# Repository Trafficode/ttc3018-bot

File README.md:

# Bark Beetle

Rebuildable configuration for a Raspberry Pi CNC monitoring host.
Current baseline: Raspberry Pi 5, Raspberry Pi Camera Rev 1.3 (OV5647),
DHT22 on GPIO17 and private Tailscale access.

- [Set up another Raspberry Pi](docs/development/setup.md)
- [Run checks and troubleshoot](docs/development/operations.md)
- [Verified hardware and software](docs/reference/baseline.md)
- [System boundaries and next components](docs/architecture/system.md)
- [Build and operate the component-based panel](docs/development/operator-ui.md)
- [Local manufacturing collection and Tractor transfer](docs/development/file-library.md)
- [Install the private Android operator app](docs/development/android-app.md)
- [Plan PCB surface measurements](docs/development/surface-plan.md)
- [Check the probe and set automatic Z zero](docs/development/z-probe.md)
- [10 mm PCB starter coupon and CAM files](docs/reference/pcb-cnc-coupon-10mm-cam.md)
- [40 mm PCB reference coupon](docs/reference/pcb-cnc-coupon-40mm.md)

Bark Beetle provides camera video, environmental telemetry and explicit manual CNC
controls through private Tailscale Serve. The operator connects USB, jogs, sets
material zero and controls the spindle. There is no automatic USB reconnect,
homing or unlock. Z probing starts only with operator confirmation and a verified
probe-input test. File jobs support explicitly started linear GRBL
programs; see [file jobs and limits](docs/development/file-jobs.md).
See the operations guide for the first supervised test.

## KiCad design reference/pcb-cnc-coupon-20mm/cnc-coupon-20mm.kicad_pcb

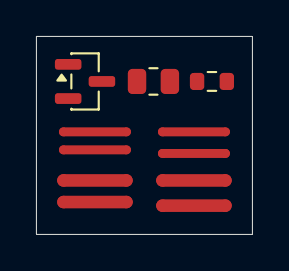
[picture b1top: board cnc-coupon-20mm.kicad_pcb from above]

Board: 2 copper layers, 12.0 x 11.0 mm, 7 parts (0 on the bottom side), 8 nets.

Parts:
Q1: SOT-23
R1: R_0805_2012Metric
R2: R_0603_1608Metric
T1: W0.5_G0.5; Pair_W0.5_G0.5
T2: W0.5_G0.7; Pair_W0.5_G0.7
T3: W0.7_G0.5; Pair_W0.7_G0.5
T4: W0.7_G0.7; Pair_W0.7_G0.7

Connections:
W0.5_G0.5_1: T1.1, T1.2
W0.5_G0.5_2: T1.3, T1.4
W0.5_G0.7_1: T2.1, T2.2
W0.5_G0.7_2: T2.3, T2.4
W0.7_G0.5_1: T3.1, T3.2
W0.7_G0.5_2: T3.3, T3.4
W0.7_G0.7_1: T4.1, T4.2
W0.7_G0.7_2: T4.3, T4.4

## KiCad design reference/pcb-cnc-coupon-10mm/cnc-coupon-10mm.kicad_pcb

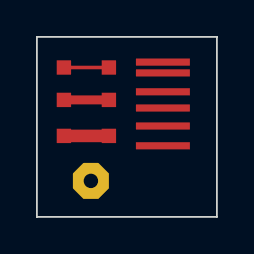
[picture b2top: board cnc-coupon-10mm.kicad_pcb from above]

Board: 2 copper layers, 10.0 x 10.0 mm, 7 parts (0 on the bottom side), 3 nets.

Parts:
G1: Gap_0.2mm
G2: Gap_0.5mm
G3: Gap_0.7mm
V1: Octagon_2mm_Drill_0.8mm
W1: Width_0.2mm
W2: Width_0.5mm
W3: Width_0.7mm

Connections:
WIDTH_0.2: W1.1, W1.2
WIDTH_0.5: W2.1, W2.2
WIDTH_0.7: W3.1, W3.2

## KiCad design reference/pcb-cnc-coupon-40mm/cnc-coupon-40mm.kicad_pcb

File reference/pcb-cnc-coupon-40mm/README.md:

# CNC PCB coupon — 40 × 40 mm, revision A

Open `cnc-coupon-40mm.kicad_pro` in KiCad 10, then open the PCB editor.
This is a passive board-only process coupon, not a powered circuit. No schematic,
machine job, feeds, speeds or fabrication acceptance are implied.

- [Test map and measurement procedure](../../docs/reference/pcb-cnc-coupon-40mm.md)
- [Layout preview](validation/layout.png)
- [Printable layout](validation/layout.pdf)
- [DRC evidence](validation/drc.json)
- [Measured native geometry](validation/geometry.json)

The width and clearance ladders cover 1.0, 0.8, 0.6, 0.5, 0.4, 0.3, 0.25
and 0.2 mm. Values below 0.4 mm are deliberately experimental. A clean DRC
with the coupon's 0.2 mm limits does not establish machining capability.

Top copper is the test surface. B.Cu contains only the native through-hole pad
rings; it is not a second-side test. KiCad's through-hole pad type does not mean
that CNC-drilled holes are plated. No electrical connection through the board
is assumed. No paste, silkscreen, mask or bottom-side machining is required.

The XY0 copper dot and auxiliary origin are 5 mm right and 5 mm down from the
top-left outline corner in the editor's top view. CAM must explicitly select
the same datum and axis convention; setting this origin is not a machine setup.
All labels are silkscreen-only reference annotations, not copper to engrave.

The custom diagnostic footprints are included in `CncCoupon.pretty`.
Standard footprints use the installed KiCad 10 libraries through `fp-lib-table`.
Scripts in `tools/` use KiCad's own Python runtime to rebuild and verify geometry.
Rebuilding replaces this generated coupon; save edited designs separately.

Use a larger blank held by the supplied CNC clamps. Keep clamps outside every
tool path. The 40 mm outline is the finished coupon, not a mandatory blank size.
Do not cut the outline until the final operation and a holding strategy exists.

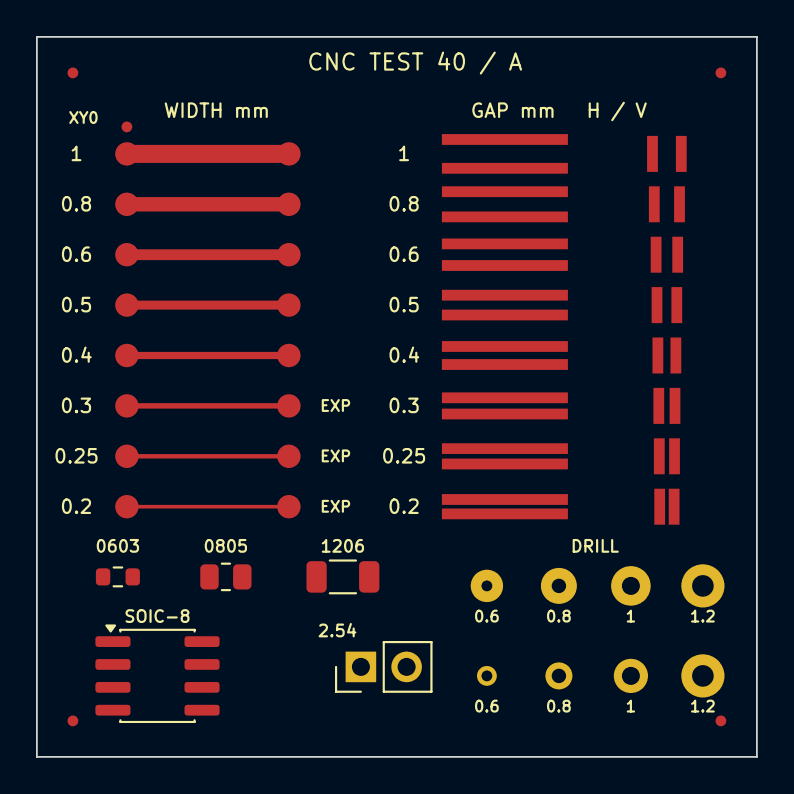
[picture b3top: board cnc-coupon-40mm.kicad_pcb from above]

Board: 2 copper layers, 40.0 x 40.0 mm, 42 parts (0 on the bottom side), 8 nets.

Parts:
D1: Drill_0.6mm_Ring_0.6mm
D2: Drill_0.8mm_Ring_0.6mm
D3: Drill_1mm_Ring_0.6mm
D4, D8: Drill_1.2mm_Ring_0.6mm
D5: Drill_0.6mm_Ring_0.25mm
D6: Drill_0.8mm_Ring_0.35mm
D7: Drill_1mm_Ring_0.45mm
F1, F2, F3, F4: Fiducial_0.6mm
G1H: Gap_1mm_H
G1V: Gap_1mm_V
G2H: Gap_0.8mm_H
G2V: Gap_0.8mm_V
G3H: Gap_0.6mm_H
G3V: Gap_0.6mm_V
G4H: Gap_0.5mm_H
G4V: Gap_0.5mm_V
G5H: Gap_0.4mm_H
G5V: Gap_0.4mm_V
G6H: Gap_0.3mm_H
G6V: Gap_0.3mm_V
G7H: Gap_0.25mm_H
G7V: Gap_0.25mm_V
G8H: Gap_0.2mm_H
G8V: Gap_0.2mm_V
J1: 2.54mm; PinHeader_1x02_P2.54mm_Vertical
O1: Fiducial_0.6mm
R1: 0603; R_0603_1608Metric
R2: 0805; R_0805_2012Metric
R3: 1206; R_1206_3216Metric
U1: SOIC-8; SOIC-8_3.9x4.9mm_P1.27mm
W1: Width_1mm
W2: Width_0.8mm
W3: Width_0.6mm
W4: Width_0.5mm
W5: Width_0.4mm
W6: Width_0.3mm
W7: Width_0.25mm
W8: Width_0.2mm

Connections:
WIDTH_0.2: W8.1, W8.2
WIDTH_0.3: W6.1, W6.2
WIDTH_0.4: W5.1, W5.2
WIDTH_0.5: W4.1, W4.2
WIDTH_0.6: W3.1, W3.2
WIDTH_0.8: W2.1, W2.2
WIDTH_0.25: W7.1, W7.2
WIDTH_1: W1.1, W1.2
